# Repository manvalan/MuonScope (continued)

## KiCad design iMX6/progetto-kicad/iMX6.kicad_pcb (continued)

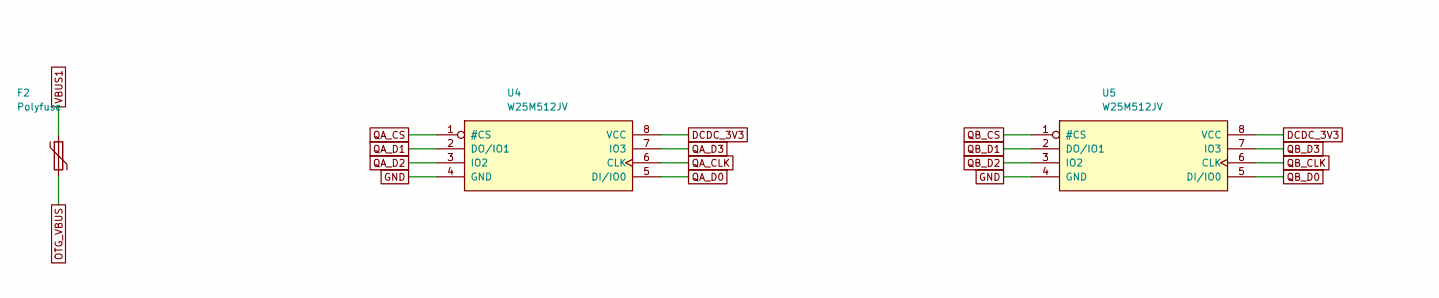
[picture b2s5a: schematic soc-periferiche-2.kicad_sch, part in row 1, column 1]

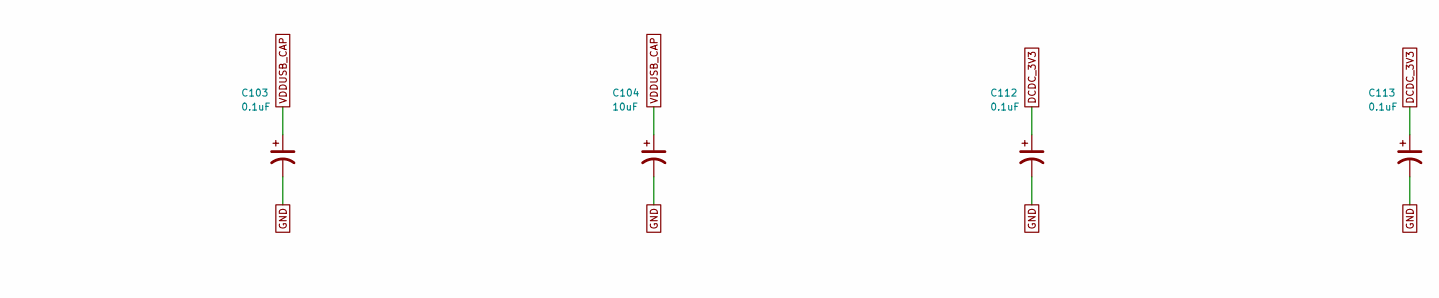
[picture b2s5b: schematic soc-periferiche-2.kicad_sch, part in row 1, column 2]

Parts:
C103, C112, C113: 0.1uF; C_0402_narrow
C104: 10uF; C_0603_narrow
F2: Polyfuse; D_0805_2012Metric
U4, U5: W25M512JV; WSON8_8x6mm

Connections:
DCDC_3V3: C112.1, C113.1, U4.8 (VCC), U5.8 (VCC); also elsewhere on the board
GND: C103.2, C104.2, C112.2, C113.2, U4.4 (GND), U5.4 (GND); also elsewhere on the board
OTG_VBUS: F2.2; also elsewhere on the board
QA_CLK: U4.6 (CLK); also elsewhere on the board
QA_CS: U4.1 (#CS); also elsewhere on the board
QA_D0: U4.5 (DI/IO0); also elsewhere on the board
QA_D1: U4.2 (DO/IO1); also elsewhere on the board
QA_D2: U4.3 (IO2); also elsewhere on the board
QA_D3: U4.7 (IO3); also elsewhere on the board
QB_CLK: U5.6 (CLK); also elsewhere on the board
QB_CS: U5.1 (#CS); also elsewhere on the board
QB_D0: U5.5 (DI/IO0); also elsewhere on the board
QB_D1: U5.2 (DO/IO1); also elsewhere on the board
QB_D2: U5.3 (IO2); also elsewhere on the board
QB_D3: U5.7 (IO3); also elsewhere on the board
VBUS1: F2.1; also elsewhere on the board
VDDUSB_CAP: C103.1, C104.1; also elsewhere on the board

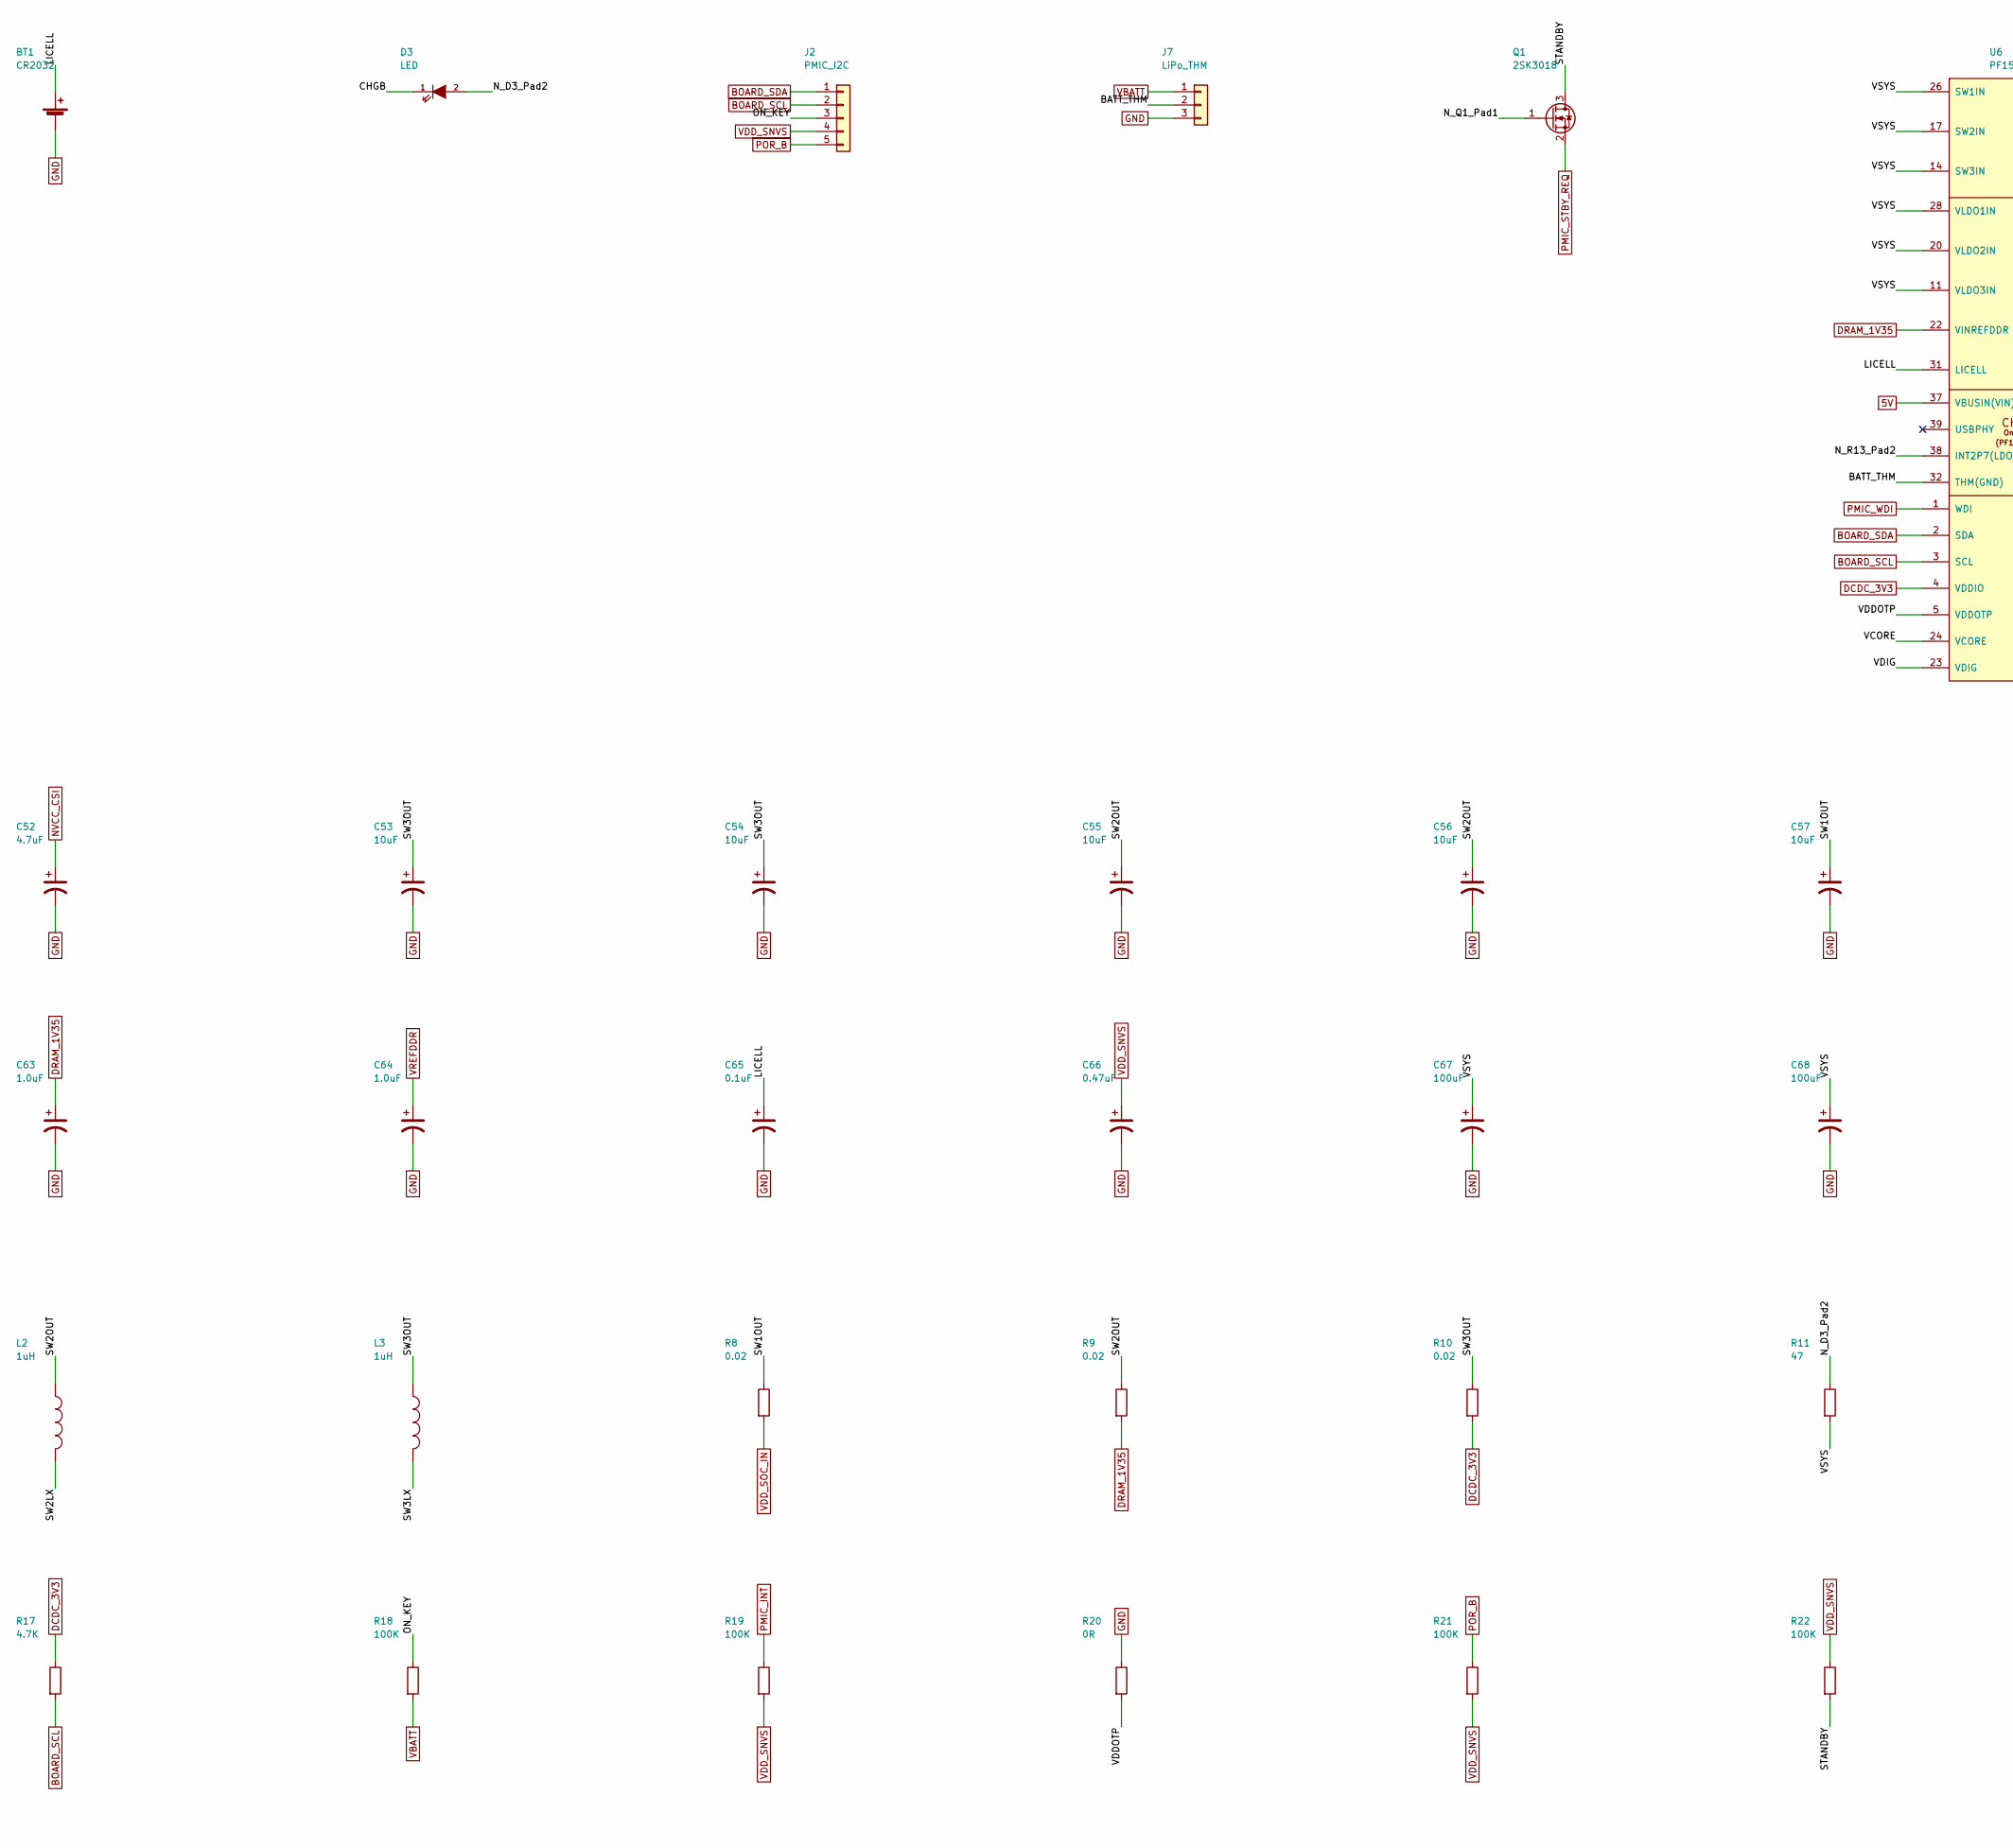
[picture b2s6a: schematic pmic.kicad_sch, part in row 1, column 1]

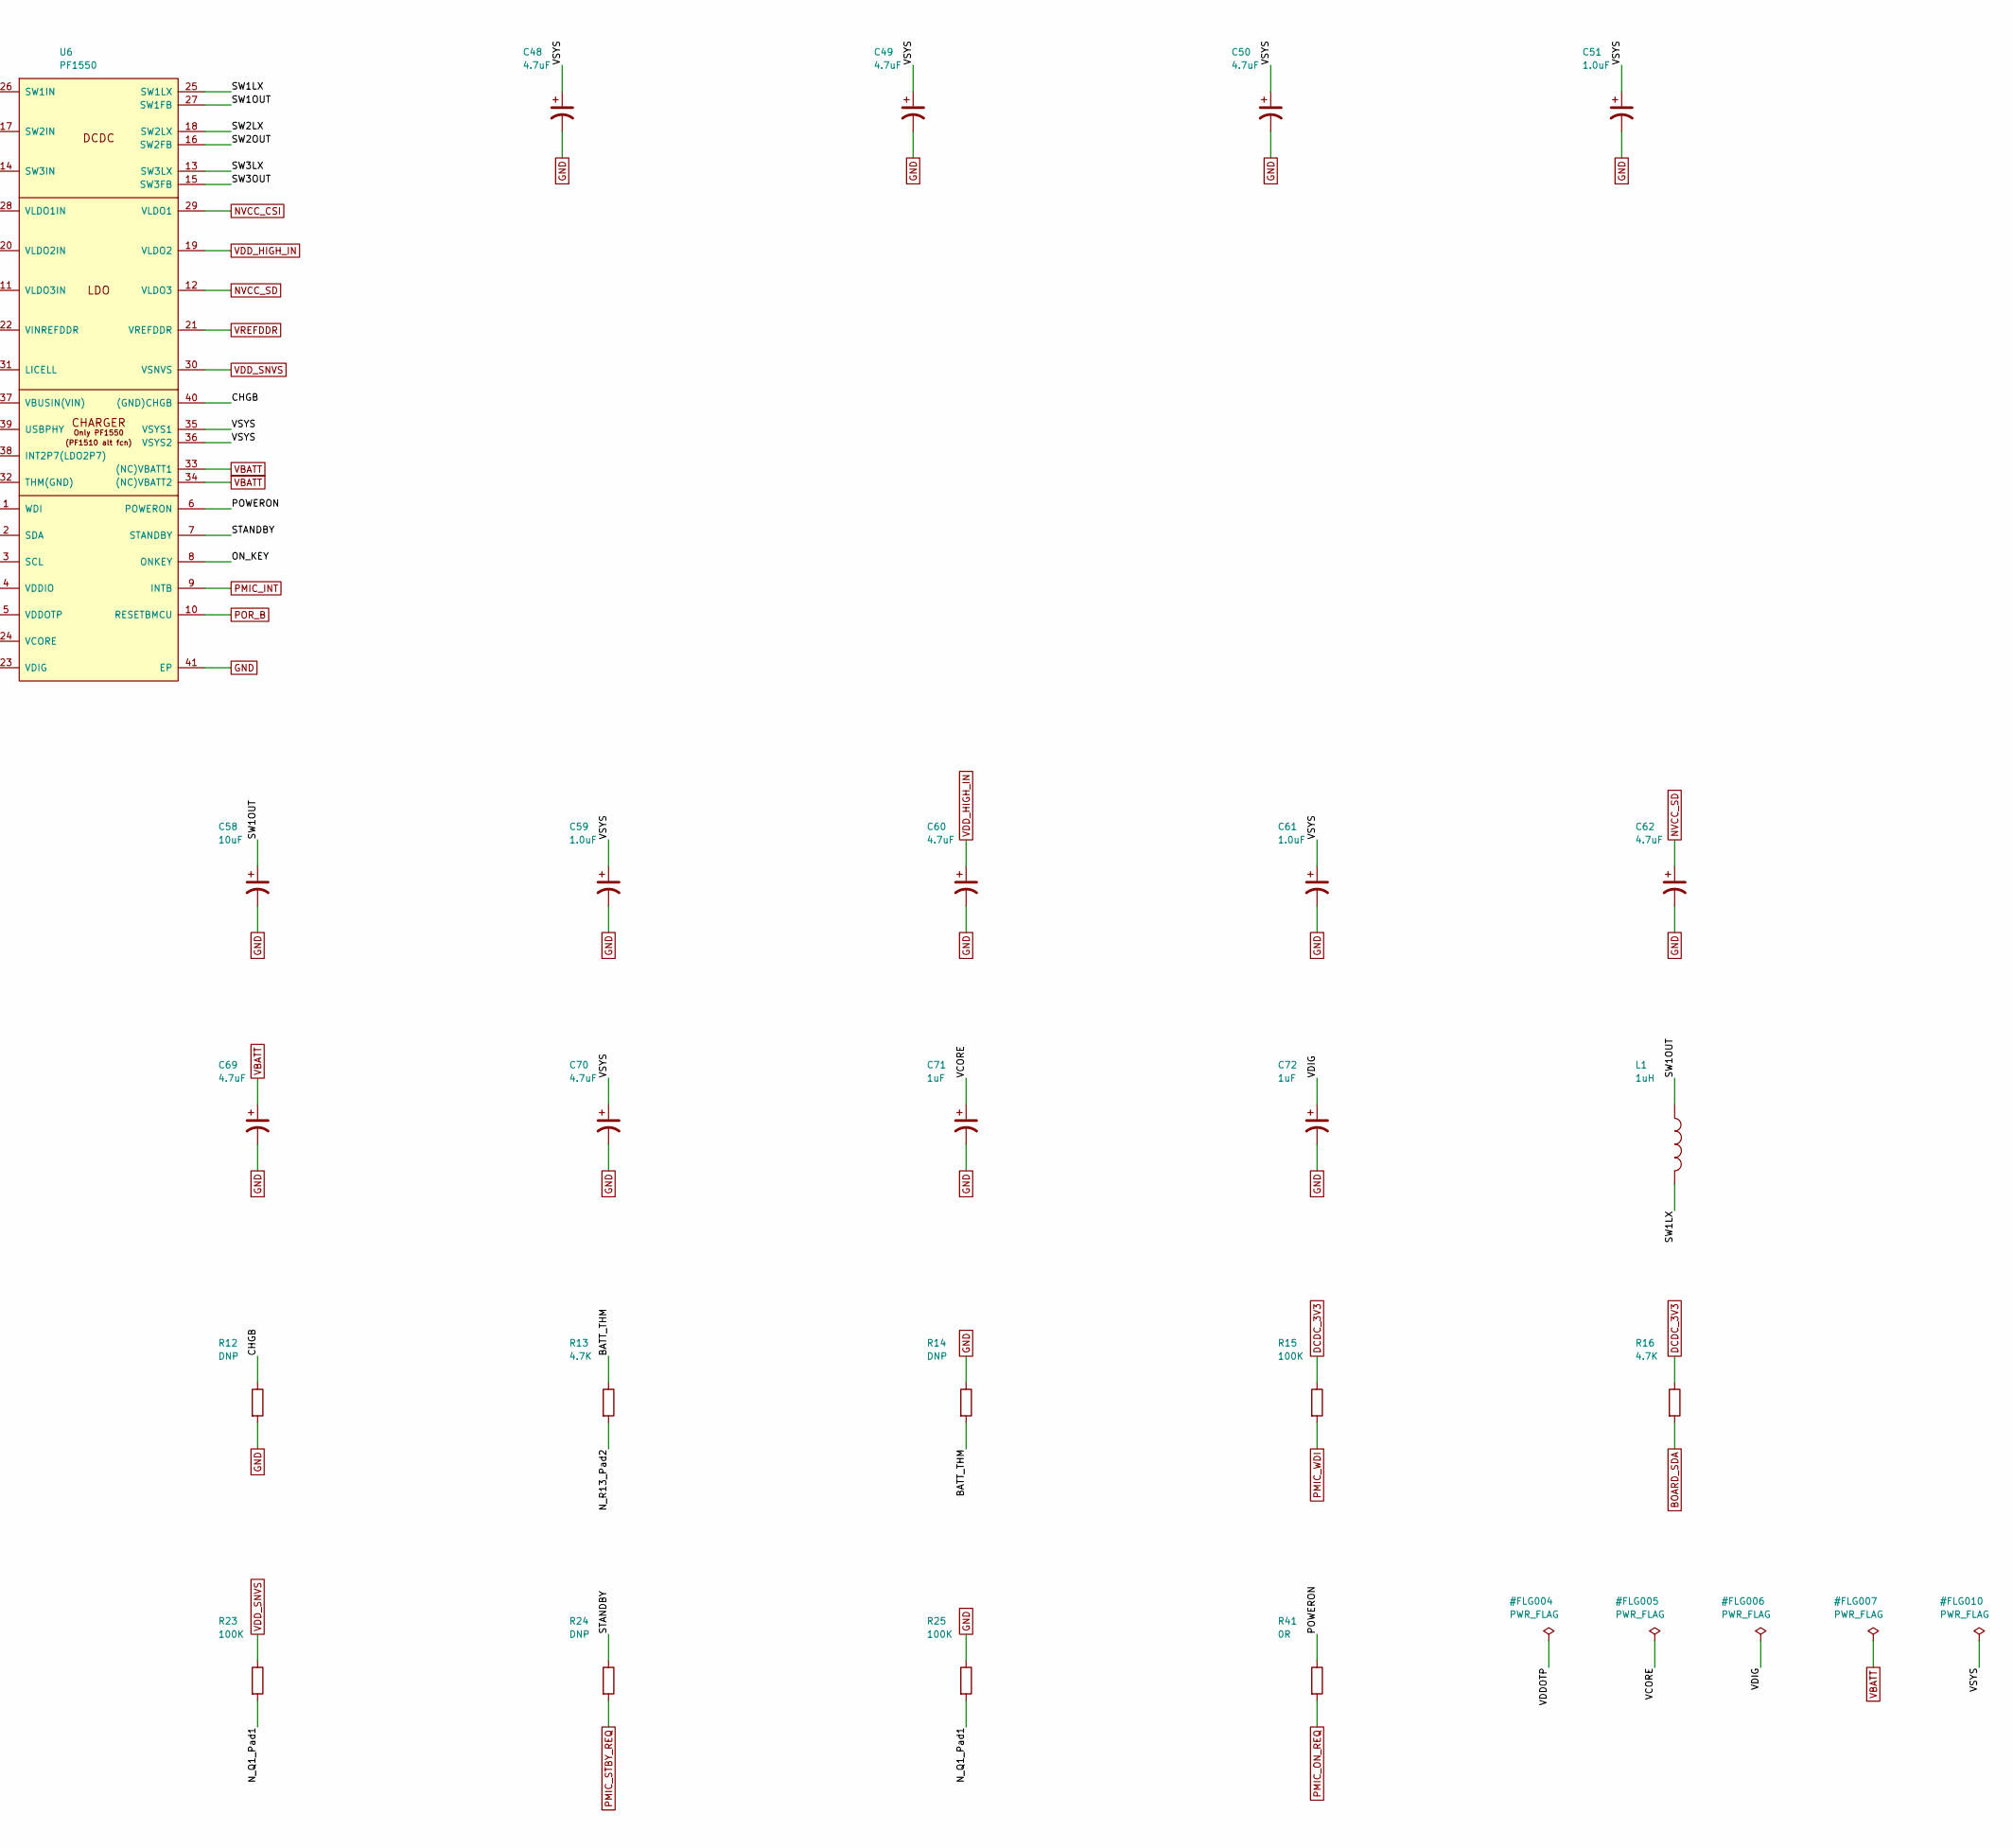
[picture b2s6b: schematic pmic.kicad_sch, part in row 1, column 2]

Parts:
BT1: CR2032; BatteryHolder_Keystone_1058_1x2032
C48, C49, C50, C52, C60, C62: 4.7uF; C_0402_narrow
C51, C59, C61, C64: 1.0uF; C_0402_narrow
C53, C54, C55, C56, C57, C58: 10uF; C_0603_narrow
C63: 1.0uF; C_0603_narrow
C65: 0.1uF; C_0603_narrow
C66: 0.47uF; C_0402_narrow
C67, C68: 100uF; C_0603_narrow
C69, C70: 4.7uF; C_0603_narrow
C71, C72: 1uF; C_0402_narrow
D3: LED; LED_0402_1005Metric
J2: PMIC_I2C; PinHeader_1x05_P2.54mm_Vertical
J7: LiPo_THM; PinHeader_1x03_P2.54mm_Vertical
L1, L2, L3: 1uH; L_0805_narrow
Q1: 2SK3018; SOT-23
R8, R9, R10: 0.02; R_0402_narrow
R11: 47; R_0402_narrow
R12, R14, R24: DNP; R_0402_narrow
R13, R16, R17: 4.7K; R_0402_narrow
R15, R18, R19, R21, R22, R23, R25: 100K; R_0402_narrow
R20, R41: 0R; R_0402_narrow
U6: PF1550; QFN-40-1EP_5x5mm_P0.4mm_EP3.6x3.6mm_ThermalVias

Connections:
5V: U6.37 (VBUSIN(VIN)); also elsewhere on the board
/PMIC PF1550/BATT_THM: J7.2, R13.1, R14.2, U6.32 (THM(GND))
/PMIC PF1550/CHGB: D3.1 (K), R12.1, U6.40 ((GND)CHGB)
/PMIC PF1550/LICELL: BT1.1 (+), C65.1, U6.31 (LICELL)
/PMIC PF1550/N_D3_Pad2: D3.2 (A), R11.1
/PMIC PF1550/N_Q1_Pad1: Q1.1 (G), R23.2, R25.2
/PMIC PF1550/N_R13_Pad2: R13.2, U6.38 (INT2P7(LDO2P7))
/PMIC PF1550/ON_KEY: J2.3, R18.1, U6.8 (ONKEY)
/PMIC PF1550/POWERON: R41.1, U6.6 (POWERON)
/PMIC PF1550/STANDBY: Q1.3 (D), R22.2, R24.1, U6.7 (STANDBY)
/PMIC PF1550/SW1LX: L1.2, U6.25 (SW1LX)
/PMIC PF1550/SW1OUT: C57.1, C58.1, L1.1, R8.1, U6.27 (SW1FB)
/PMIC PF1550/SW2LX: L2.2, U6.18 (SW2LX)
/PMIC PF1550/SW2OUT: C55.1, C56.1, L2.1, R9.1, U6.16 (SW2FB)
/PMIC PF1550/SW3LX: L3.2, U6.13 (SW3LX)
/PMIC PF1550/SW3OUT: C53.1, C54.1, L3.1, R10.1, U6.15 (SW3FB)
/PMIC PF1550/VCORE: C71.1, U6.24 (VCORE)
/PMIC PF1550/VDDOTP: R20.2, U6.5 (VDDOTP)
/PMIC PF1550/VDIG: C72.1, U6.23 (VDIG)
/PMIC PF1550/VSYS: C48.1, C49.1, C50.1, C51.1, C59.1, C61.1, C67.1, C68.1, C70.1, R11.2, U6.11 (VLDO3IN), U6.14 (SW3IN), U6.17 (SW2IN), U6.20 (VLDO2IN), U6.26 (SW1IN), U6.28 (VLDO1IN), U6.35 (VSYS1), U6.36 (VSYS2)
BOARD_SCL: J2.2, R17.2, U6.3 (SCL); also elsewhere on the board
BOARD_SDA: J2.1, R16.2, U6.2 (SDA); also elsewhere on the board
DCDC_3V3: R10.2, R15.1, R16.1, R17.1, U6.4 (VDDIO); also elsewhere on the board
DRAM_1V35: C63.1, R9.2, U6.22 (VINREFDDR); also elsewhere on the board
GND: BT1.2 (-), C48.2, C49.2, C50.2, C51.2, C52.2, C53.2, C54.2, C55.2, C56.2, C57.2, C58.2, C59.2, C60.2, C61.2, C62.2, C63.2, C64.2, C65.2, C66.2, C67.2, C68.2, C69.2, C70.2, C71.2, C72.2, J7.3, R12.2, R14.1, R20.1, R25.1, U6.41 (EP); also elsewhere on the board
NVCC_CSI: C52.1, U6.29 (VLDO1); also elsewhere on the board
NVCC_SD: C62.1, U6.12 (VLDO3); also elsewhere on the board
PMIC_INT: R19.1, U6.9 (INTB); also elsewhere on the board
PMIC_ON_REQ: R41.2; also elsewhere on the board
PMIC_STBY_REQ: Q1.2 (S), R24.2; also elsewhere on the board
PMIC_WDI: R15.2, U6.1 (WDI); also elsewhere on the board
POR_B: J2.5, R21.1, U6.10 (RESETBMCU); also elsewhere on the board
VBATT: C69.1, J7.1, R18.2, U6.33 ((NC)VBATT1), U6.34 ((NC)VBATT2); also elsewhere on the board
VDD_HIGH_IN: C60.1, U6.19 (VLDO2); also elsewhere on the board
VDD_SNVS: C66.1, J2.4, R19.2, R21.2, R22.1, R23.1, U6.30 (VSNVS); also elsewhere on the board
VDD_SOC_IN: R8.2; also elsewhere on the board
VREFDDR: C64.1, U6.21 (VREFDDR); also elsewhere on the board

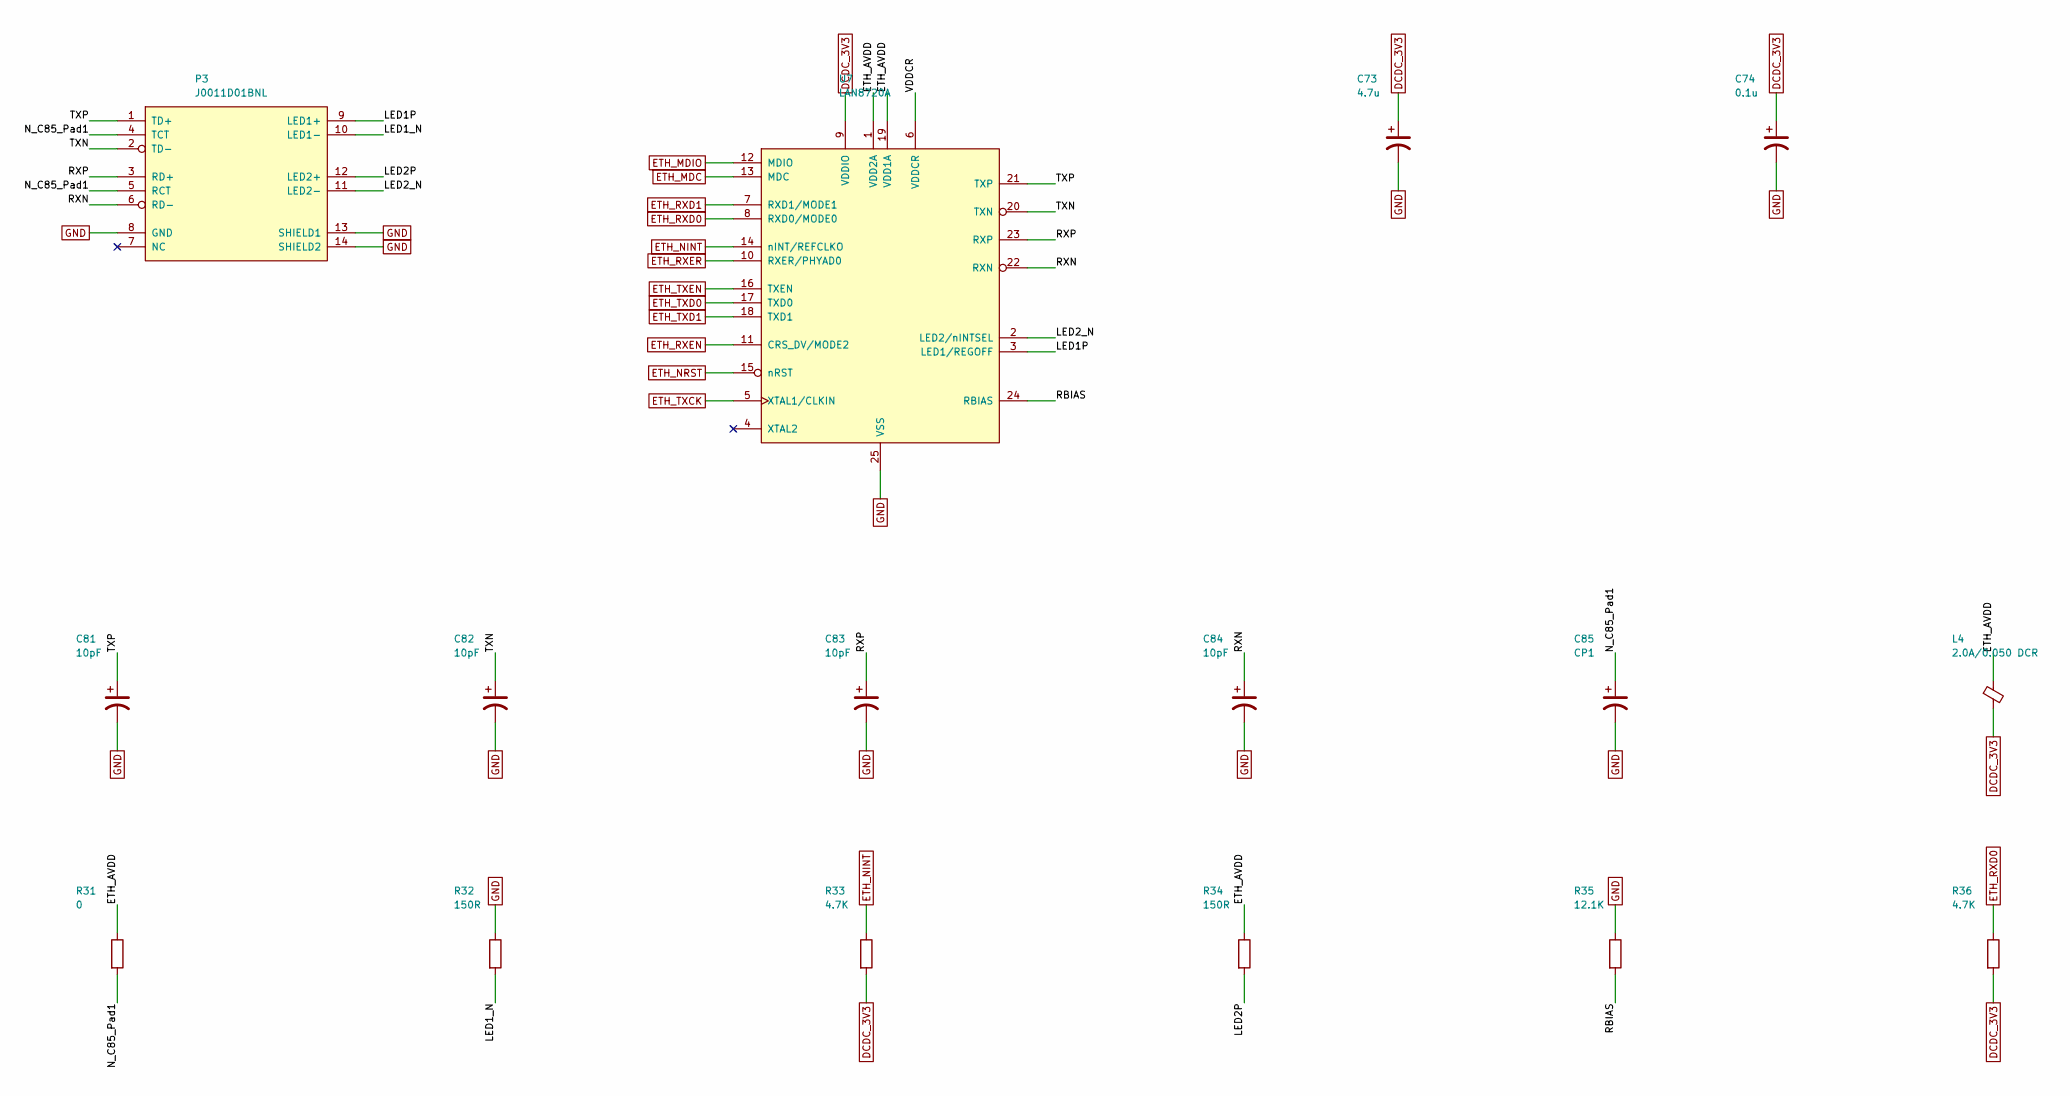
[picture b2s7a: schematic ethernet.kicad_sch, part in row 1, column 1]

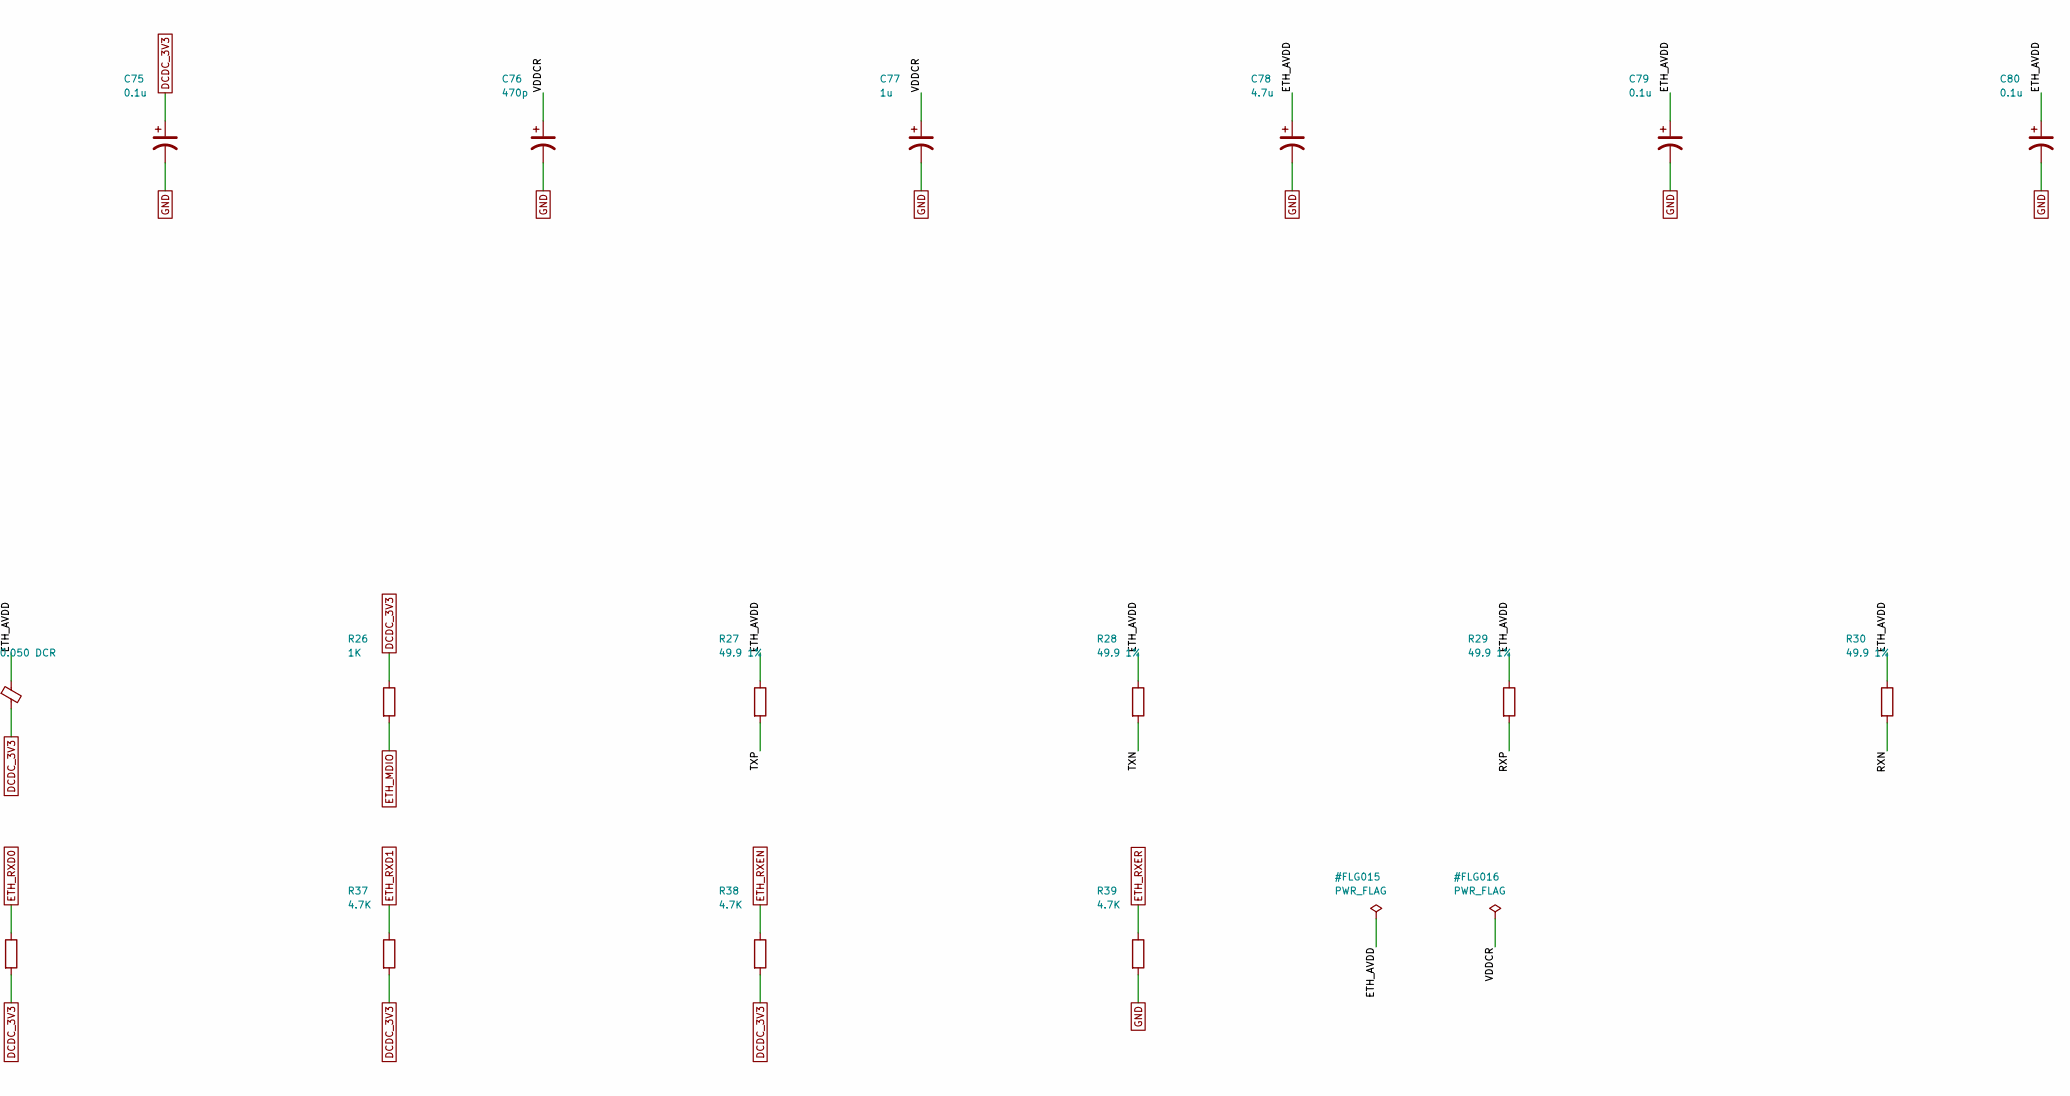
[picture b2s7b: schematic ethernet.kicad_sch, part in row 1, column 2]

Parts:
C73, C78: 4.7u; C_0603_narrow
C74, C75, C79, C80: 0.1u; C_0402_narrow
C76: 470p; C_0402_narrow
C77: 1u; C_0603_narrow
C81, C82, C83, C84: 10pF; C_0402_narrow
C85: CP1; C_0402_narrow
L4: 2.0A/0.050 DCR; R_0805_2012Metric
P3: J0011D01BNL; MTJ-88TX1-FSD-D1LH-M4Y
R26: 1K; R_0402_narrow
R27, R28, R29, R30: 49.9 1%; R_0402_narrow
R31: 0; R_0402_narrow
R32, R34: 150R; R_0402_narrow
R33, R36, R37, R38, R39: 4.7K; R_0402_narrow
R35: 12.1K; R_0402_narrow
U7: LAN8720A; QFN-24-1EP_4x4mm_P0.5mm_EP2.6x2.6mm_ThermalVias

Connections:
/Ethernet/ETH_AVDD: C78.1, C79.1, C80.1, L4.1, R27.1, R28.1, R29.1, R30.1, R31.1, R34.1, U7.1 (VDD2A), U7.19 (VDD1A)
/Ethernet/LED1P: P3.9 (LED1+), U7.3 (LED1/REGOFF)
/Ethernet/LED1_N: P3.10 (LED1-), R32.2
/Ethernet/LED2P: P3.12 (LED2+), R34.2
/Ethernet/LED2_N: P3.11 (LED2-), U7.2 (LED2/nINTSEL)
/Ethernet/N_C85_Pad1: C85.1, P3.4 (TCT), P3.5 (RCT), R31.2
/Ethernet/RBIAS: R35.2, U7.24 (RBIAS)
/Ethernet/RXN: C84.1, P3.6 (RD-), R30.2, U7.22 (RXN)
/Ethernet/RXP: C83.1, P3.3 (RD+), R29.2, U7.23 (RXP)
/Ethernet/TXN: C82.1, P3.2 (TD-), R28.2, U7.20 (TXN)
/Ethernet/TXP: C81.1, P3.1 (TD+), R27.2, U7.21 (TXP)
/Ethernet/VDDCR: C76.1, C77.1, U7.6 (VDDCR)
DCDC_3V3: C73.1, C74.1, C75.1, L4.2, R26.1, R33.2, R36.2, R37.2, R38.2, U7.9 (VDDIO); also elsewhere on the board
ETH_MDC: U7.13 (MDC); also elsewhere on the board
ETH_MDIO: R26.2, U7.12 (MDIO); also elsewhere on the board
ETH_NINT: R33.1, U7.14 (nINT/REFCLKO); also elsewhere on the board
ETH_NRST: U7.15 (nRST); also elsewhere on the board
ETH_RXD0: R36.1, U7.8 (RXD0/MODE0); also elsewhere on the board
ETH_RXD1: R37.1, U7.7 (RXD1/MODE1); also elsewhere on the board
ETH_RXEN: R38.1, U7.11 (CRS_DV/MODE2); also elsewhere on the board
ETH_RXER: R39.1, U7.10 (RXER/PHYAD0); also elsewhere on the board
ETH_TXCK: U7.5 (XTAL1/CLKIN); also elsewhere on the board
ETH_TXD0: U7.17 (TXD0); also elsewhere on the board
ETH_TXD1: U7.18 (TXD1); also elsewhere on the board
ETH_TXEN: U7.16 (TXEN); also elsewhere on the board
GND: C73.2, C74.2, C75.2, C76.2, C77.2, C78.2, C79.2, C80.2, C81.2, C82.2, C83.2, C84.2, C85.2, P3.8 (GND), P3.13 (SHIELD1), P3.14 (SHIELD2), R32.1, R35.1, R39.2, U7.25 (VSS); also elsewhere on the board

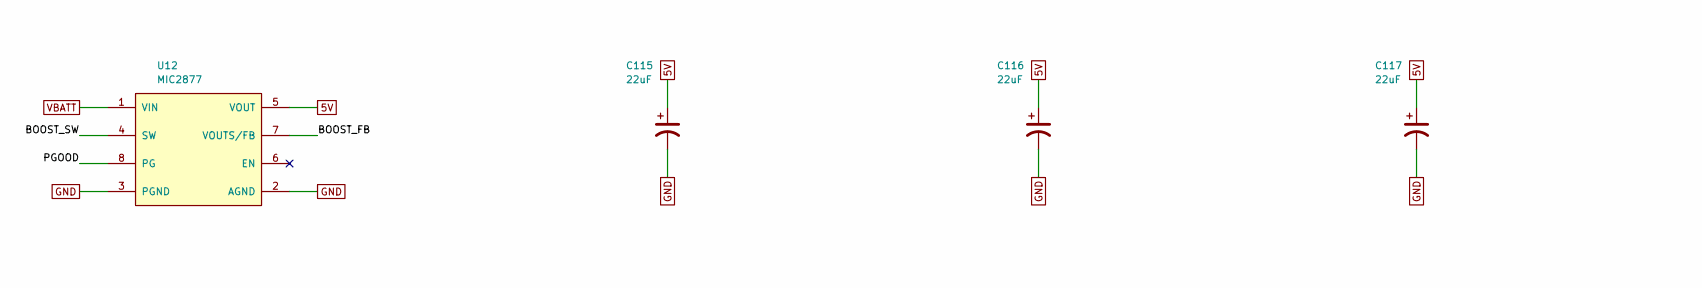
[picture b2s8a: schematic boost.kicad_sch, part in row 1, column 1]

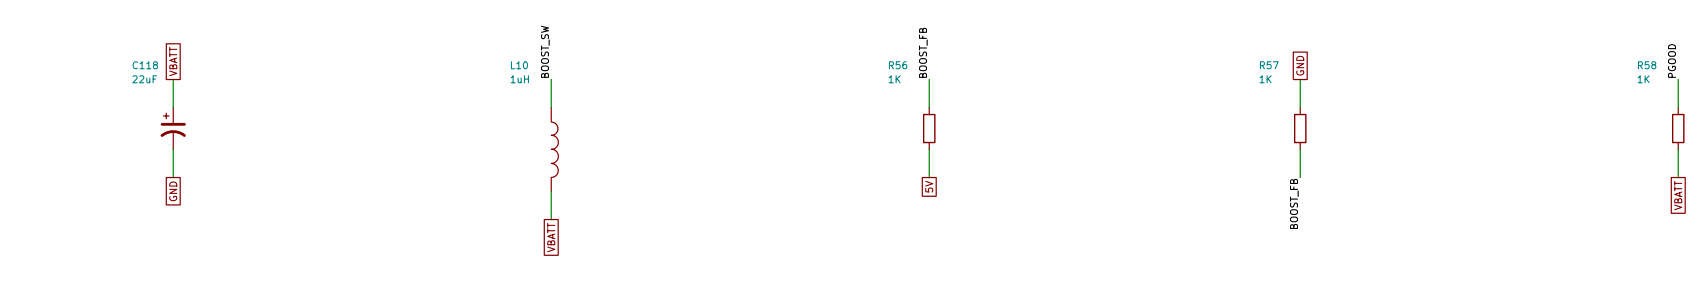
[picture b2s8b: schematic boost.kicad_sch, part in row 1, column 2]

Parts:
C115, C116, C117, C118: 22uF; C_0603_narrow
L10: 1uH; L_Bourns-SRN4018
R56, R57, R58: 1K; R_0402_narrow
U12: MIC2877

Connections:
5V: C115.1, C116.1, C117.1, R56.2, U12.5 (VOUT); also elsewhere on the board
/Boost batteria/BOOST_FB: R56.1, R57.2, U12.7 (VOUTS/FB)
/Boost batteria/BOOST_SW: L10.1, U12.4 (SW)
/Boost batteria/PGOOD: R58.1, U12.8 (PG)
GND: C115.2, C116.2, C117.2, C118.2, R57.1, U12.2 (AGND), U12.3 (PGND); also elsewhere on the board
VBATT: C118.1, L10.2, R58.2, U12.1 (VIN); also elsewhere on the board

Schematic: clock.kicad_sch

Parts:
C96, C97: 18p; C_0402_narrow
C98, C99: 18pF; C_0402_narrow
C100: 0.1uF; C_0402_narrow
C101: 1.0uF; C_0402_narrow
FB1: Bead; R_0402_narrow
J5: JTAG; PinHeader_2x05_P1.00mm_Vertical_SMD
R52: 4.7k; R_0402_narrow
R53: 1M; R_0402_narrow
R54: 499; R_0402_narrow
R55: 2.2M; R_0402_narrow
SB1, SB2, SB3, SB4: 4.7K; R_0402_narrow
XTAL2: 24MHz 50ppm; Oscillator_SMD_EuroQuartz_XO32-4Pin_3.2x2.5mm
Y1: 32.768 kHz; Crystal_SMD_3215-2Pin_3.2x1.5mm

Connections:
BOOT0: SB3.1, SB4.1; also elsewhere on the board
BOOT1: SB1.1, SB2.1; also elsewhere on the board
DCDC_3V3: J5.1; also elsewhere on the board
GND: C96.2, C97.2, C98.2, C99.2, C100.2, C101.2, J5.3, J5.5, J5.9, R52.1, R54.2, R55.2, SB2.2, SB4.2, XTAL2.2, XTAL2.4; also elsewhere on the board
IMX_XTALI: C99.1, R53.1, R55.1, XTAL2.3; also elsewhere on the board
IMX_XTALO: C98.1, R53.2, R54.1, XTAL2.1; also elsewhere on the board
JTAG_MOD: R52.2; also elsewhere on the board
JTAG_TCK: J5.4; also elsewhere on the board
JTAG_TDI: J5.8; also elsewhere on the board
JTAG_TDO: J5.6; also elsewhere on the board
JTAG_TMS: J5.2; also elsewhere on the board
JTAG_TRST_B: J5.7; also elsewhere on the board
POR_B: J5.10; also elsewhere on the board
RTC_XTALI: C97.1, Y1.2; also elsewhere on the board
RTC_XTALO: C96.1, Y1.1; also elsewhere on the board
VDDA_ADC: C100.1, C101.1, FB1.2; also elsewhere on the board
VDD_HIGH_IN: FB1.1; also elsewhere on the board
VDD_SNVS: SB1.2, SB3.2; also elsewhere on the board

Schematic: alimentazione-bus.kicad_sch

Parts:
C201, C202: 10uF/25V; C_1206_3216Metric
C203: 100nF/50V; C_0603_1608Metric
C204, C208: 100nF; C_0603_1608Metric
C205: 100pF; C_0603_1608Metric
C206, C207, C211: 47uF/10V; C_1206_3216Metric
C209, C210: 1uF/10V; C_0603_1608Metric
D8: SMF5.0A; D_SMF; MPN SMF5.0A; LCSC C151296
J8: TYPE-C-31-M-12; USB-C_SMD-TYPE-C-31-M-12_1; MPN TYPE-C-31-M-12; LCSC C165948
L11: 3.3uH/8A; L_Coilcraft_XAL6030-XXX; MPN XAL6030-332MEC
R201: 169k 1%; R_0603_1608Metric
R202: 36.1k 1%; R_0603_1608Metric
R203: 100k; R_0603_1608Metric
R204: 73.2k 1%; R_0603_1608Metric
R205, R208, R210, R212: 10k 1%; R_0603_1608Metric
R206: 20k; R_0603_1608Metric
R207: 32.4k 1%; R_0603_1608Metric
R209, R211: 46.4k 1%; R_0603_1608Metric
R213: 22.1k 1%; R_0603_1608Metric
R214: 10k; R_0603_1608Metric
R215, R216: 5.1k; R_0603_1608Metric
U13: TPS56637RPAR; VQFN-HR-10_L3.0-W3.0_RPA; MPN TPS56637RPAR; LCSC C841386
U14: TPS2121RUXR; IC_TPS2121RUXR; MPN TPS2121RUXR; LCSC C485916
U15: USBLC6-2SC6; SOT-23-6; MPN USBLC6-2SC6; LCSC C7519

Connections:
5V: C211.1, U14.1 (OUT), U14.1_1 (OUT), U14.8 (OUT), U14.8_1 (OUT); also elsewhere on the board
/Alimentazione bus e USB-C/5V_BUCK: C206.1, C207.1, C209.1, L11.2, R203.1, R204.1, R206.1, R207.1, R209.1, U14.7 (IN1), U14.7_1 (IN1)
/Alimentazione bus e USB-C/BUCK_BST: C204.1, U13.7 (BOOT)
/Alimentazione bus e USB-C/BUCK_EN: R201.2, R202.1, U13.1 (EN)
/Alimentazione bus e USB-C/BUCK_FB: C205.2, R204.2, R205.1, U13.2 (FB)
/Alimentazione bus e USB-C/BUCK_FF: C205.1, R206.2
/Alimentazione bus e USB-C/BUCK_PG: R203.2, U13.4 (PG)
/Alimentazione bus e USB-C/BUCK_SW: C204.2, L11.1, U13.6 (SW)
/Alimentazione bus e USB-C/MUX_ILM: R213.1, U14.10 (ILIM)
/Alimentazione bus e USB-C/MUX_OV1: R209.2, R210.1, U14.5 (OV1)
/Alimentazione bus e USB-C/MUX_OV2: R211.2, R212.1, U14.4 (OV2)
/Alimentazione bus e USB-C/MUX_PR1: R207.2, R208.1, U14.6 (PR1)
/Alimentazione bus e USB-C/MUX_SS: C208.1, U14.11 (SS)
/Alimentazione bus e USB-C/PWR_SRC_ST: R214.2, U14.9 (ST)
/Alimentazione bus e USB-C/USB1_CC1: J8.A5 (CC1), R215.1
/Alimentazione bus e USB-C/USB1_CC2: J8.B5 (CC2), R216.1
DCDC_3V3: R214.1; also elsewhere on the board
GND: C201.2, C202.2, C203.2, C206.2, C207.2, C208.2, C209.2, C210.2, C211.2, D8.2 (A2), J8.1 (EH), J8.2 (EH), J8.3 (EH), J8.4 (EH), J8.A1B12 (GND), J8.B1A12 (GND), R202.2, R205.2, R208.2, R210.2, R212.2, R213.2, R215.2, R216.2, U13.3 (AGND), U13.9 (PGND), U14.3 (CP2), U14.12 (GND), U15.2 (GND); also elsewhere on the board
OTG_VBUS: D8.1 (A1), J8.A4B9 (VBUS), J8.B4A9 (VBUS), U15.5 (VBUS); also elsewhere on the board
USB1_DM: J8.A7 (DN1), J8.B7 (DN2), U15.3 (I/O2), U15.4 (I/O2); also elsewhere on the board
USB1_DP: J8.A6 (DP1), J8.B6 (DP2), U15.1 (I/O1), U15.6 (I/O1); also elsewhere on the board
VBUS1: C210.1, R211.1, U14.2 (IN2), U14.2_1 (IN2); also elsewhere on the board
VIN_SYS: C201.1, C202.1, C203.1, R201.1, U13.8 (VIN); also elsewhere on the board

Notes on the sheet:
VIN_SYS 12 V dal BUS_POWER -> TPS56637 5 V -> TPS2121 IN1 (priorita'). IN2 = VBUS della USB-C 1 (dopo il polyfuse F2 di nanoberry). Uscita -> 5V di nanoberry (VBUSIN del PF1550).
Il boost MIC2877 di nanoberry resta sul 5V (alimentazione da LiPo): il TPS2121 blocca la corrente inversa. Circuiti come sulle schede MIKILAB (SchedaIMX6ULL-SD).
TPS56637: EN 169k/36.1k, FB 73.2k/10k = 4.99 V, FF 20k + 100 pF
TPS2121: PR1 4.49 V, OV 5.98 V, ILM 22.1k, SS 100 nF; PWR_SRC_ST con 10k
USB-C 1: sink 5.1k su CC1/CC2
